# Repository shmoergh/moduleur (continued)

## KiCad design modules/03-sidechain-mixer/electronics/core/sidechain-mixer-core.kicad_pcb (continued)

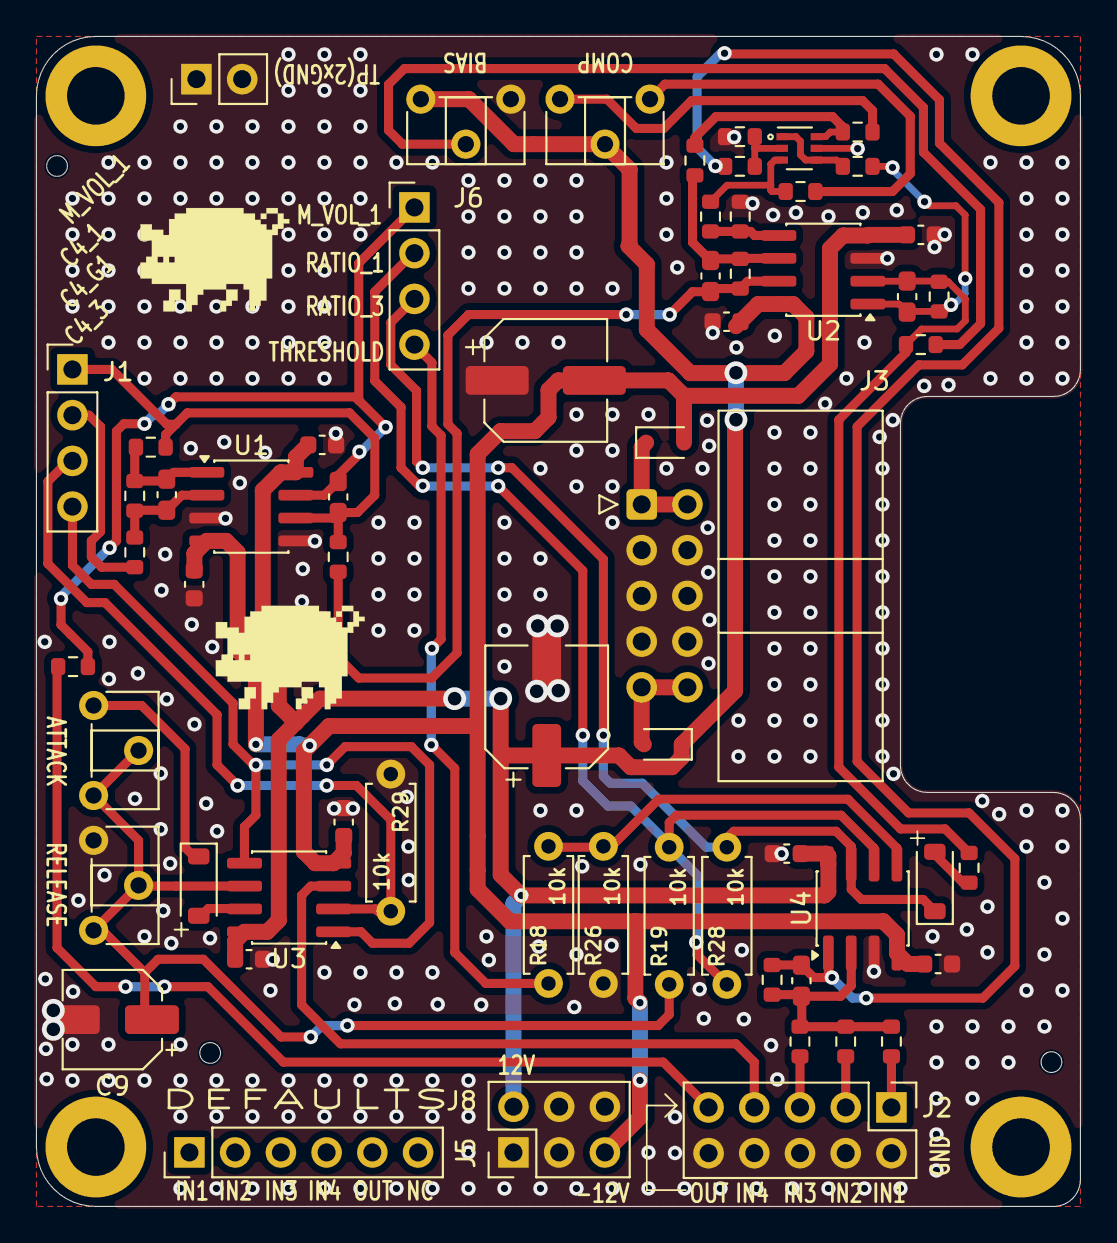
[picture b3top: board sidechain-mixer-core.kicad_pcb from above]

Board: 2 copper layers, 58.0 x 65.0 mm, 66 parts (0 on the bottom side), 39 nets.

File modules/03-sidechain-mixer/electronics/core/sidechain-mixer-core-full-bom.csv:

"Reference","Qty","Value","Exclude from BOM","Footprint","LCSC","Mouser Part no.","Part URL","Vendor","CHECKED"
"C1,C2,C3,C4,C5,C6,C7,C8","8","100n","","Capacitor_SMD:C_0603_1608Metric","C14663","","","JLCPCB","YES"
"C9","1","10u","","Capacitor_SMD:CP_Elec_5x5.4","C30110","","","JLCPCB","YES"
"C10,C11,C12,C13,C14","5","47p","","Capacitor_SMD:C_0603_1608Metric_Pad1.08x0.95mm_HandSolder","C1671","","","JLCPCB","YES"
"C23,C24","2","100u","","Capacitor_SMD:CP_Elec_6.3x7.7","C2836442","","","JLCPCB","YES"
"D1,D2","2","1N4148","","Diode_SMD:D_SOD-123","C81598","","","JLCPCB","YES"
"D6,D7","2","1N5817","","Diode_SMD:D_SOD-323","C5190152","","","JLCPCB","YES"
"J1,J6","2","Conn_01x04","","Connector_PinHeader_2.54mm:PinHeader_1x04_P2.54mm_Vertical","","200-HTSW10407TS ","https://mou.sr/3UfnMcJ","Mouser","YES"
"J2","1","Conn_02x05_Odd_Even","","Connector_PinHeader_2.54mm:PinHeader_2x05_P2.54mm_Vertical","","200-HTSW10507TD ","https://mou.sr/3MXhCO3","Mouser","YES"
"J3","1","Conn_02x05_Odd_Even","","Connector_IDC:IDC-Header_2x05_P2.54mm_Horizontal","","571-5103310-1","https://mou.sr/3GwYxj9","Mouser","YES"
"J4","1","Conn_01x02","","Connector_PinHeader_2.54mm:PinHeader_1x02_P2.54mm_Vertical","","200-HTSW10207TS","https://mou.sr/3IruU3e","Mouser","YES"
"J5","1","Conn_02x03_Odd_Even","","Connector_PinHeader_2.54mm:PinHeader_2x03_P2.54mm_Vertical","","200-TSW10307TD","https://mou.sr/4liCQlU","Mouser","YES"
"J8","1","Conn_01x06","","Connector_PinHeader_2.54mm:PinHeader_1x06_P2.54mm_Vertical","","200-HTSW10607TS","https://mou.sr/3YpdCIF","Mouser","YES"
"Q1","1","BC847BS","","Package_TO_SOT_SMD:SOT-363_SC-70-6","C5380687","","","JLCPCB","YES"
"R1,R2,R3,R4,R5,R6,R7,R9,R10,R16,R17","11","100k","","Resistor_SMD:R_0603_1608Metric","C25803","","","JLCPCB","YES"
"R8","1","220","","Resistor_SMD:R_0603_1608Metric","C22962","","","JLCPCB","YES"
"R11","1","1k","","Resistor_SMD:R_0603_1608Metric","C21190","","","JLCPCB","YES"
"R12,R21,R22","3","10k","","Resistor_SMD:R_0603_1608Metric","C25804","","","JLCPCB","YES"
"R13","1","33k","","Resistor_SMD:R_0603_1608Metric","C4216","","","JLCPCB","YES"
"R14,R15","2","200k","","Resistor_SMD:R_0603_1608Metric","C25811","","","JLCPCB","YES"
"R18,R19,R26,R28,R29","5","10k","","Shmoergh_Custom_Footprints:R_Axial_DIN0207_L6.3mm_D2.5mm_P7.62mm_Horizontal","","603-MFR-25FRF5210K","https://mou.sr/4aLzHIM","Mouser","YES"
"R23,R24","2","470k","","Resistor_SMD:R_0603_1608Metric","C23178","","","JLCPCB","YES"
"RV_ATTACK1,RV_RELEASE1","2","10-100k","","Potentiometer_THT:Potentiometer_ACP_CA6-H2,5_Horizontal","","774-06TR4AA103CP","https://mou.sr/44pTlq5","Mouser","YES"
"RV_BIAS1","1","100k","","Potentiometer_THT:Potentiometer_ACP_CA6-H2,5_Horizontal","","774-06TR4AA104CP","https://mou.sr/4oMQfnb","Mouser","YES"
"RV_COMP1","1","10k","","Potentiometer_THT:Potentiometer_ACP_CA6-H2,5_Horizontal","","774-06TR4AA103CP","https://mou.sr/44pTlq5","Mouser","YES"
"U1,U2,U3,U4","4","TL072","","Package_SO:SOIC-8_3.9x4.9mm_P1.27mm","C6961","","","JLCPCB","YES"
"H1,H2,H3,H4","4","MountingHole","Excluded from BOM","MountingHole:MountingHole_3.2mm_M3_DIN965_Pad","","","","Mouser",""

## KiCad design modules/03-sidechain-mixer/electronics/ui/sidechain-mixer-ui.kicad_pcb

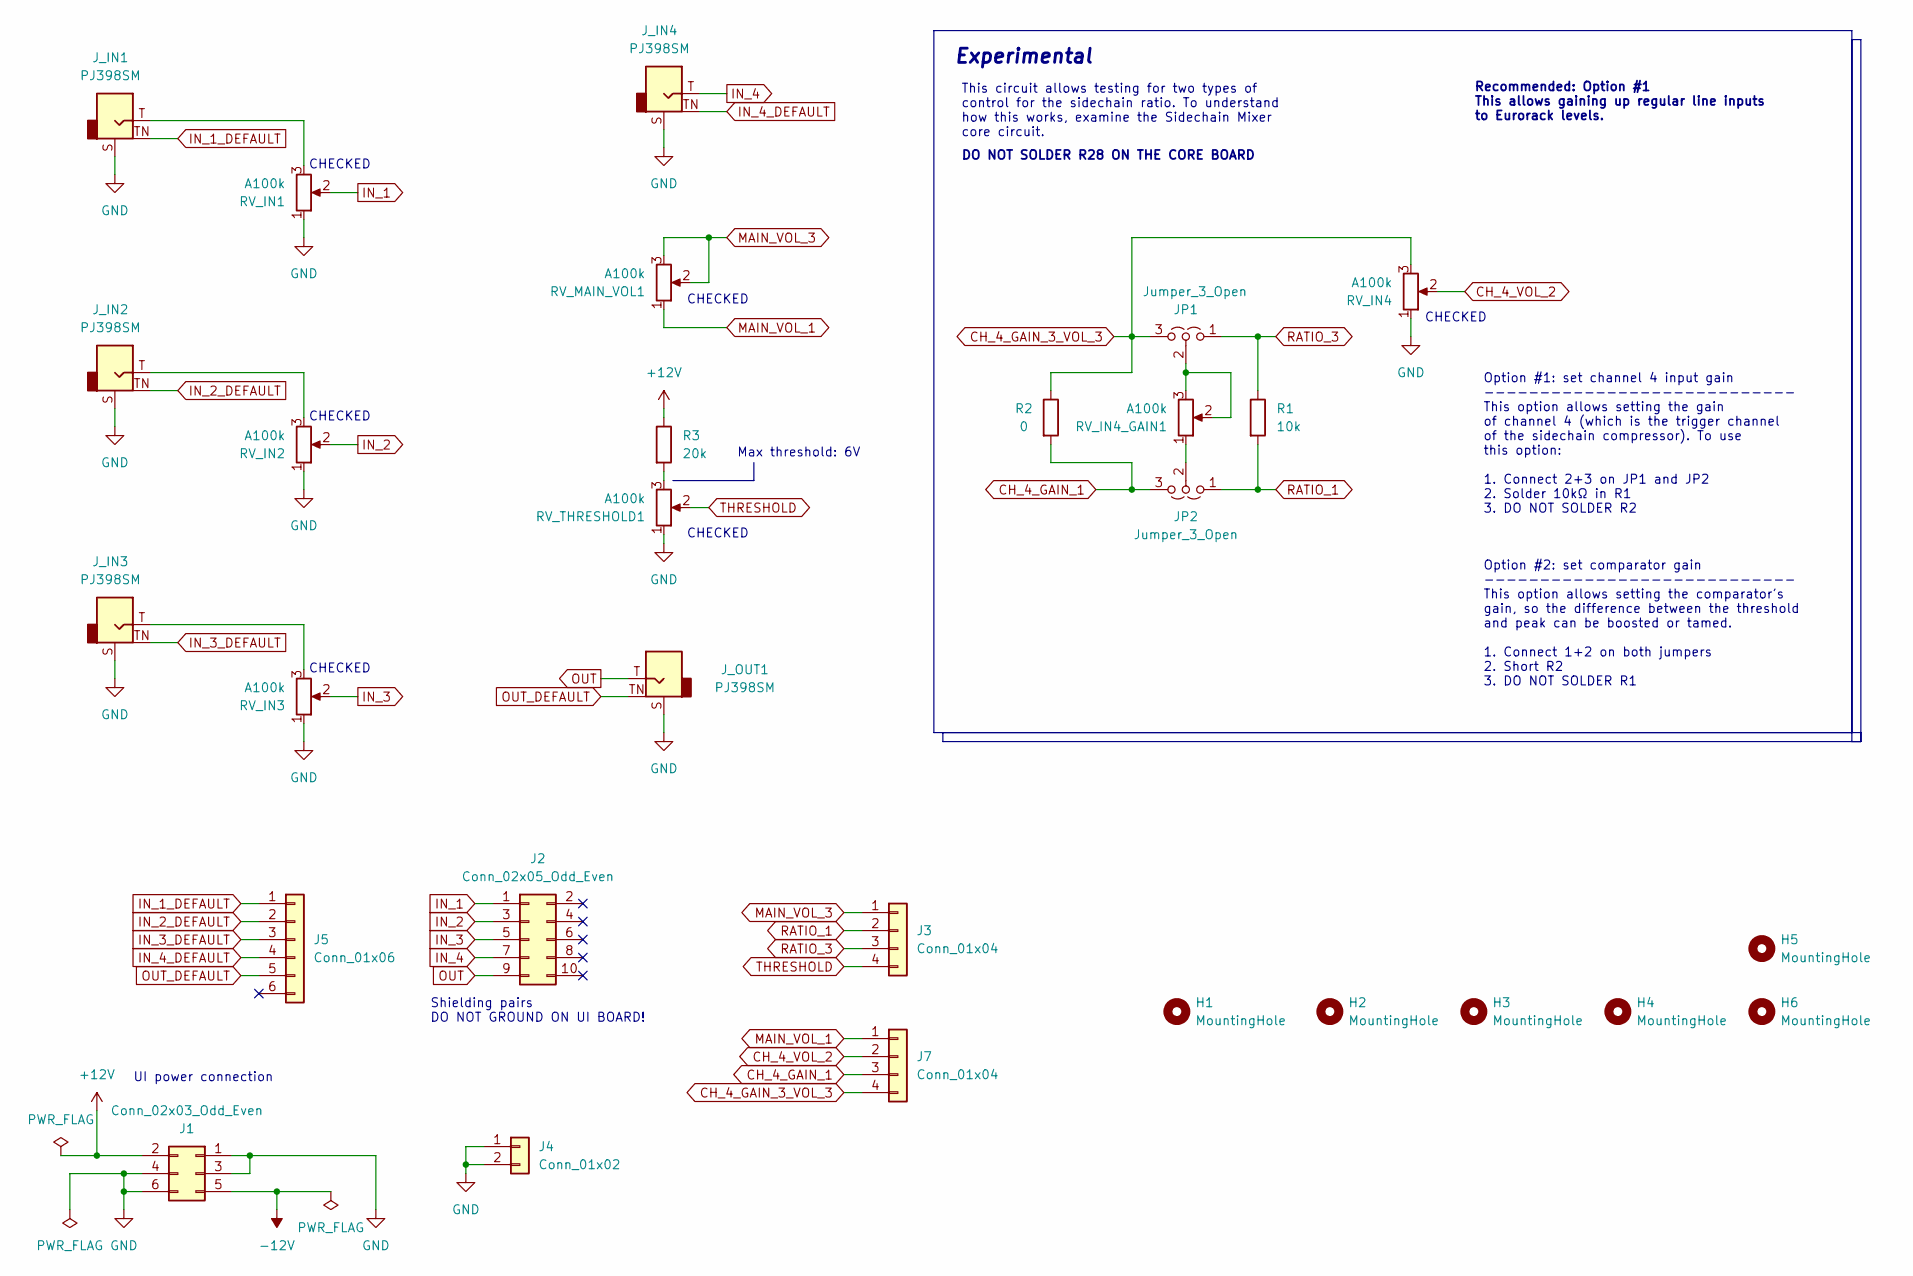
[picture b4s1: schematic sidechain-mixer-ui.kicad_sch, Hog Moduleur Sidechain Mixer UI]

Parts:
H1, H2, H3, H4, H5, H6: MountingHole; MountingHole_3.2mm_M3_DIN965_Pad
J1: Conn_02x03_Odd_Even; PinSocket_2x03_P2.54mm_Vertical; Part no. 200-SSW10301TD
J2: Conn_02x05_Odd_Even; PinSocket_2x05_P2.54mm_Vertical; Part no. 200-SSW10501TD
J3, J7: Conn_01x04; PinSocket_1x04_P2.54mm_Vertical; Part no. 200-SSW10401TMS
J4: Conn_01x02; PinSocket_1x02_P2.54mm_Vertical; Part no. 200-SSW10201TS
J5: Conn_01x06; PinSocket_1x06_P2.54mm_Vertical; Part no. 200-SSW10601TS
JP1, JP2: Jumper_3_Open; PinHeader_1x03_P2.54mm_Vertical
J_IN1, J_IN2, J_IN3, J_IN4: PJ398SM; Jack_3.5mm_QingPu_WQP-PJ398SM_Vertical_CircularHoles; Part no. PJ398SM
J_OUT1: PJ398SM; Jack_3.5mm_QingPu_WQP-PJ398SM_Vertical_CircularHoles; Part no. PJ398SM
R1: 10k; R_Axial_DIN0207_L6.3mm_D2.5mm_P7.62mm_Horizontal; Part no. 603-MFR-25FRF5210K
R2: 0; R_Axial_DIN0207_L6.3mm_D2.5mm_P7.62mm_Horizontal
R3: 20k; R_Axial_DIN0207_L6.3mm_D2.5mm_P7.62mm_Horizontal; Part no. 603-MFR-25FRF5220K
RV_IN1, RV_IN2, RV_IN3: A100k; TRIM_PTA3043-2010CIA503; Part no. 652-PTA30432015A104
RV_IN4, RV_IN4_GAIN1: A100k; Potentiometer_Bourns_Single-PTV09A; Part no. 652-PTV09A-4025UA104
RV_MAIN_VOL1: A100k; Potentiometer_Bourns_Single-PTV09A; Part no. 652-PTV09A-4025UA104
RV_THRESHOLD1: A100k; Potentiometer_Bourns_Single-PTV09A; Part no. 652-PTV09A-4025UA104

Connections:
+12V: J1.2, R3.1
-12V: J1.5
CH_4_GAIN_1: J7.3, JP2.3 (B), R2.2
CH_4_GAIN_3_VOL_3: J7.4, JP1.3 (B), R2.1, RV_IN4.3
CH_4_VOL_2: J7.2, RV_IN4.2
GND: J1.1, J1.3, J1.4, J1.6, J4.1, J4.2, J_IN1.S, J_IN2.S, J_IN3.S, J_IN4.S, J_OUT1.S, RV_IN1.1, RV_IN2.1, RV_IN3.1, RV_IN4.1, RV_THRESHOLD1.1
IN_1: J2.1, RV_IN1.2
IN_1_DEFAULT: J5.1, J_IN1.TN
IN_2: J2.3, RV_IN2.2
IN_2_DEFAULT: J5.2, J_IN2.TN
IN_3: J2.5, RV_IN3.2
IN_3_DEFAULT: J5.3, J_IN3.TN
IN_4: J2.7, J_IN4.T
IN_4_DEFAULT: J5.4, J_IN4.TN
MAIN_VOL_1: J7.1, RV_MAIN_VOL1.1
MAIN_VOL_3: J3.1, RV_MAIN_VOL1.2, RV_MAIN_VOL1.3
unnamed: JP1.2 (C), RV_IN4_GAIN1.2, RV_IN4_GAIN1.3
unnamed: JP2.2 (C), RV_IN4_GAIN1.1
unnamed: J_IN1.T, RV_IN1.3
unnamed: J_IN2.T, RV_IN2.3
unnamed: J_IN3.T, RV_IN3.3
unnamed: R3.2, RV_THRESHOLD1.3
OUT: J2.9, J_OUT1.T
OUT_DEFAULT: J5.5, J_OUT1.TN
RATIO_1: J3.2, JP2.1 (A), R1.2
RATIO_3: J3.3, JP1.1 (A), R1.1
THRESHOLD: J3.4, RV_THRESHOLD1.2

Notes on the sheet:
Recommended: Option #1 This allows gaining up regular line inputs to Eurorack levels.
Option #2: set comparator gain ---------------------------- This option allows setting the comparator's gain, so the difference between the threshold and peak can be boosted or tamed. 1. Connect 1+2 on both jumpers 2. Short R2 3. DO NOT SOLDER R1
Max threshold: 6V
CHECKED
This circuit allows testing for two types of control for the sidechain ratio. To understand how this works, examine the Sidechain Mixer core circuit.
UI power connection
Option #1: set channel 4 input gain ---------------------------- This option allows setting the gain of channel 4 (which is the trigger channel of the sidechain compressor). To use this option: 1. Connect 2+3 on JP1 and JP2 2. Solder 10kΩ in R1 3. DO NOT SOLDER R2
DO NOT SOLDER R28 ON THE CORE BOARD
Experimental
Shielding pairs DO NOT GROUND ON UI BOARD!

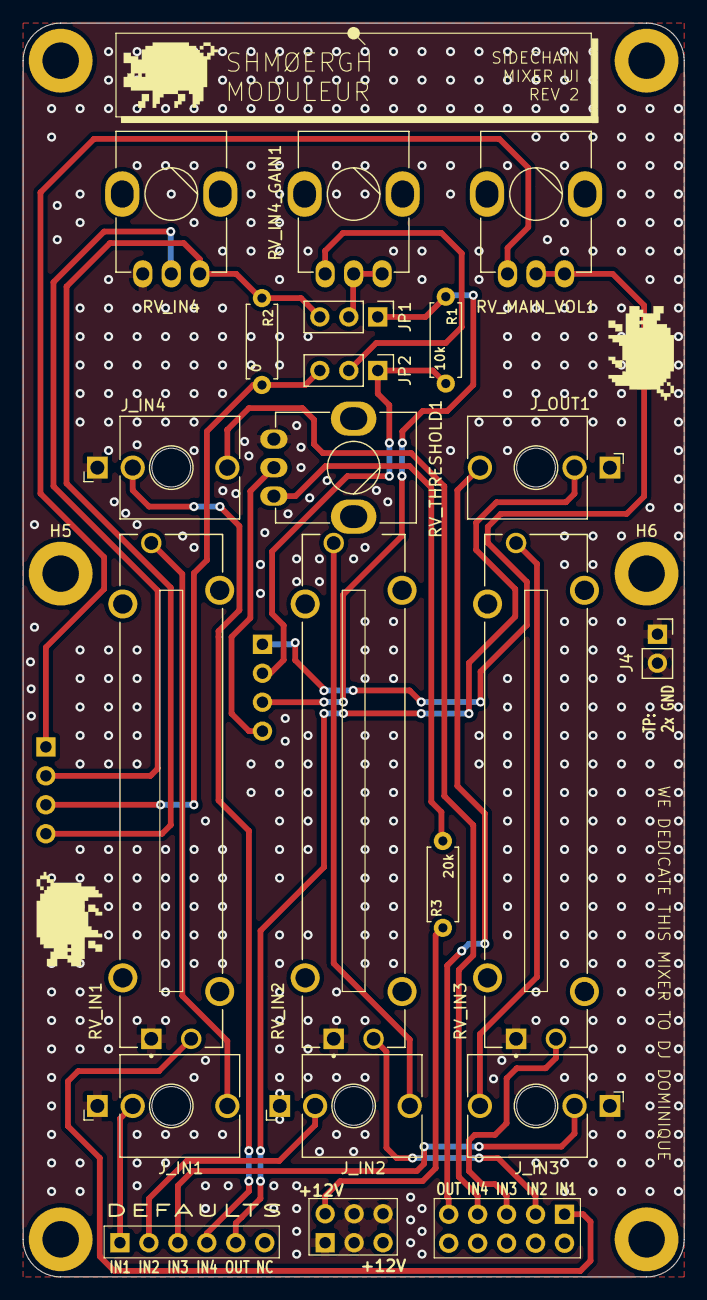
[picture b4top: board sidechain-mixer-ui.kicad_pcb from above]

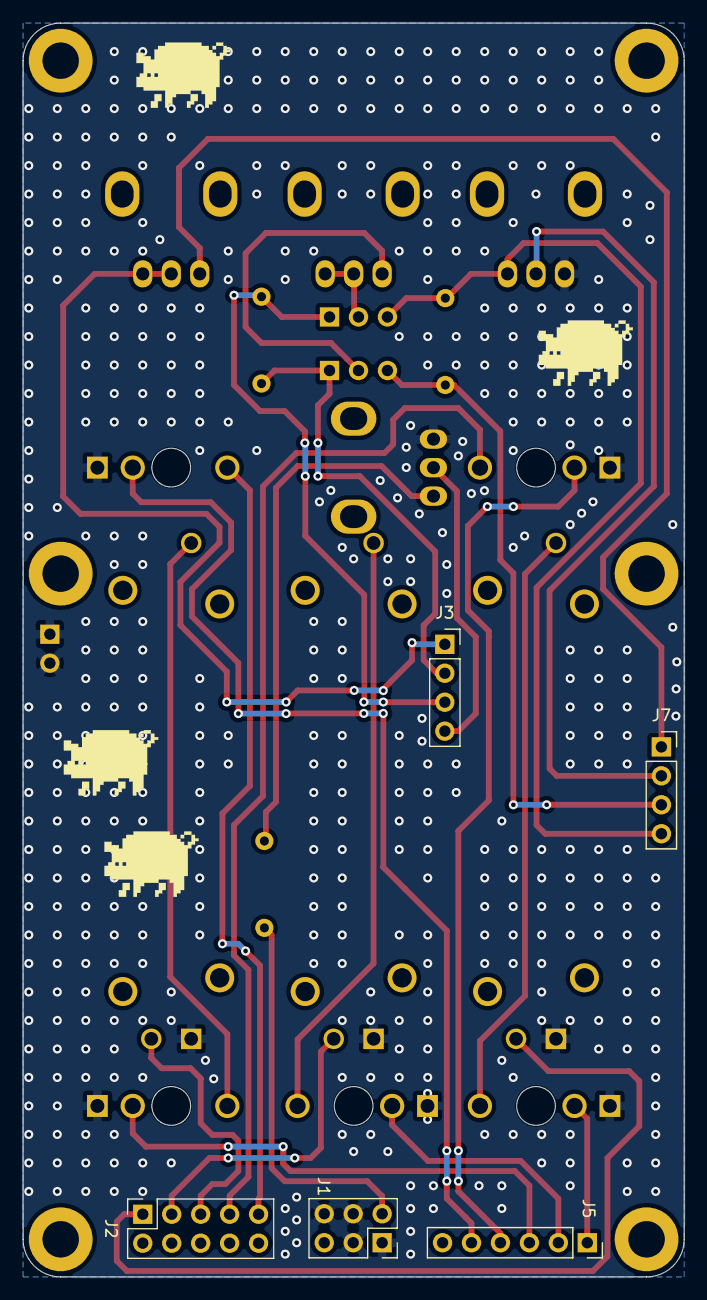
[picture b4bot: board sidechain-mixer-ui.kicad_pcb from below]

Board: 2 copper layers, 58.0 x 110.0 mm, 29 parts (5 on the bottom side), 26 nets.

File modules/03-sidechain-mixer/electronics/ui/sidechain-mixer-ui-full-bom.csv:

"Reference","Qty","Value","DNP","Exclude from BOM","Exclude from Board","Footprint","Datasheet","Part no.","Part URL","Vendor","Note"
"J1","1","Conn_02x03_Odd_Even","","","","Connector_PinSocket_2.54mm:PinSocket_2x03_P2.54mm_Vertical","~","200-SSW10301TD","https://mou.sr/3GIDVEr","Mouser",""
"J2","1","Conn_02x05_Odd_Even","","","","Connector_PinSocket_2.54mm:PinSocket_2x05_P2.54mm_Vertical","~","200-SSW10501TD","https://mou.sr/4lVCZM9","Mouser",""
"J3,J7","2","Conn_01x04","","","","Connector_PinSocket_2.54mm:PinSocket_1x04_P2.54mm_Vertical","~","200-SSW10401TMS","https://mou.sr/4kxE3Vr","Mouser",""
"J4","1","Conn_01x02","","","","Connector_PinSocket_2.54mm:PinSocket_1x02_P2.54mm_Vertical","~","200-SSW10201TS","https://mou.sr/4lBvdHe","Mouser",""
"J5","1","Conn_01x06","","","","Connector_PinSocket_2.54mm:PinSocket_1x06_P2.54mm_Vertical","~","200-SSW10601TS","https://mou.sr/4lnf48h","Mouser",""
"J_IN1,J_IN2,J_IN3,J_IN4,J_OUT1","5","PJ398SM","","","","Shmoergh_Custom_Footprints:Jack_3.5mm_QingPu_WQP-PJ398SM_Vertical_CircularHoles","~","PJ398SM","https://www.thonk.co.uk/shop/thonkiconn/","Thonk",""
"R1","1","10k","","","","Shmoergh_Custom_Footprints:R_Axial_DIN0207_L6.3mm_D2.5mm_P7.62mm_Horizontal","~","603-MFR-25FRF5210K","https://mou.sr/4aLzHIM","Mouser",""
"R2","1","0","","","","Shmoergh_Custom_Footprints:R_Axial_DIN0207_L6.3mm_D2.5mm_P7.62mm_Horizontal","~","","","",""
"R3","1","20k","","","","Shmoergh_Custom_Footprints:R_Axial_DIN0207_L6.3mm_D2.5mm_P7.62mm_Horizontal","~","603-MFR-25FRF5220K","https://mou.sr/3PSKVAZ","Mouser",""
"RV_IN1,RV_IN2,RV_IN3","3","A100k","","","","PTA3043-2010CIA503:TRIM_PTA3043-2010CIA503","~","652-PTA30432015A104 ","https://mou.sr/45jtvn7","Mouser",""
"RV_IN4,RV_IN4_GAIN1,RV_MAIN_VOL1,RV_THRESHOLD1","4","A100k","","","","Shmoergh_Custom_Footprints:Potentiometer_Bourns_Single-PTV09A","~","652-PTV09A-4025UA104 ","https://mou.sr/47O2sTG","Mouser","Knurled Shaft"

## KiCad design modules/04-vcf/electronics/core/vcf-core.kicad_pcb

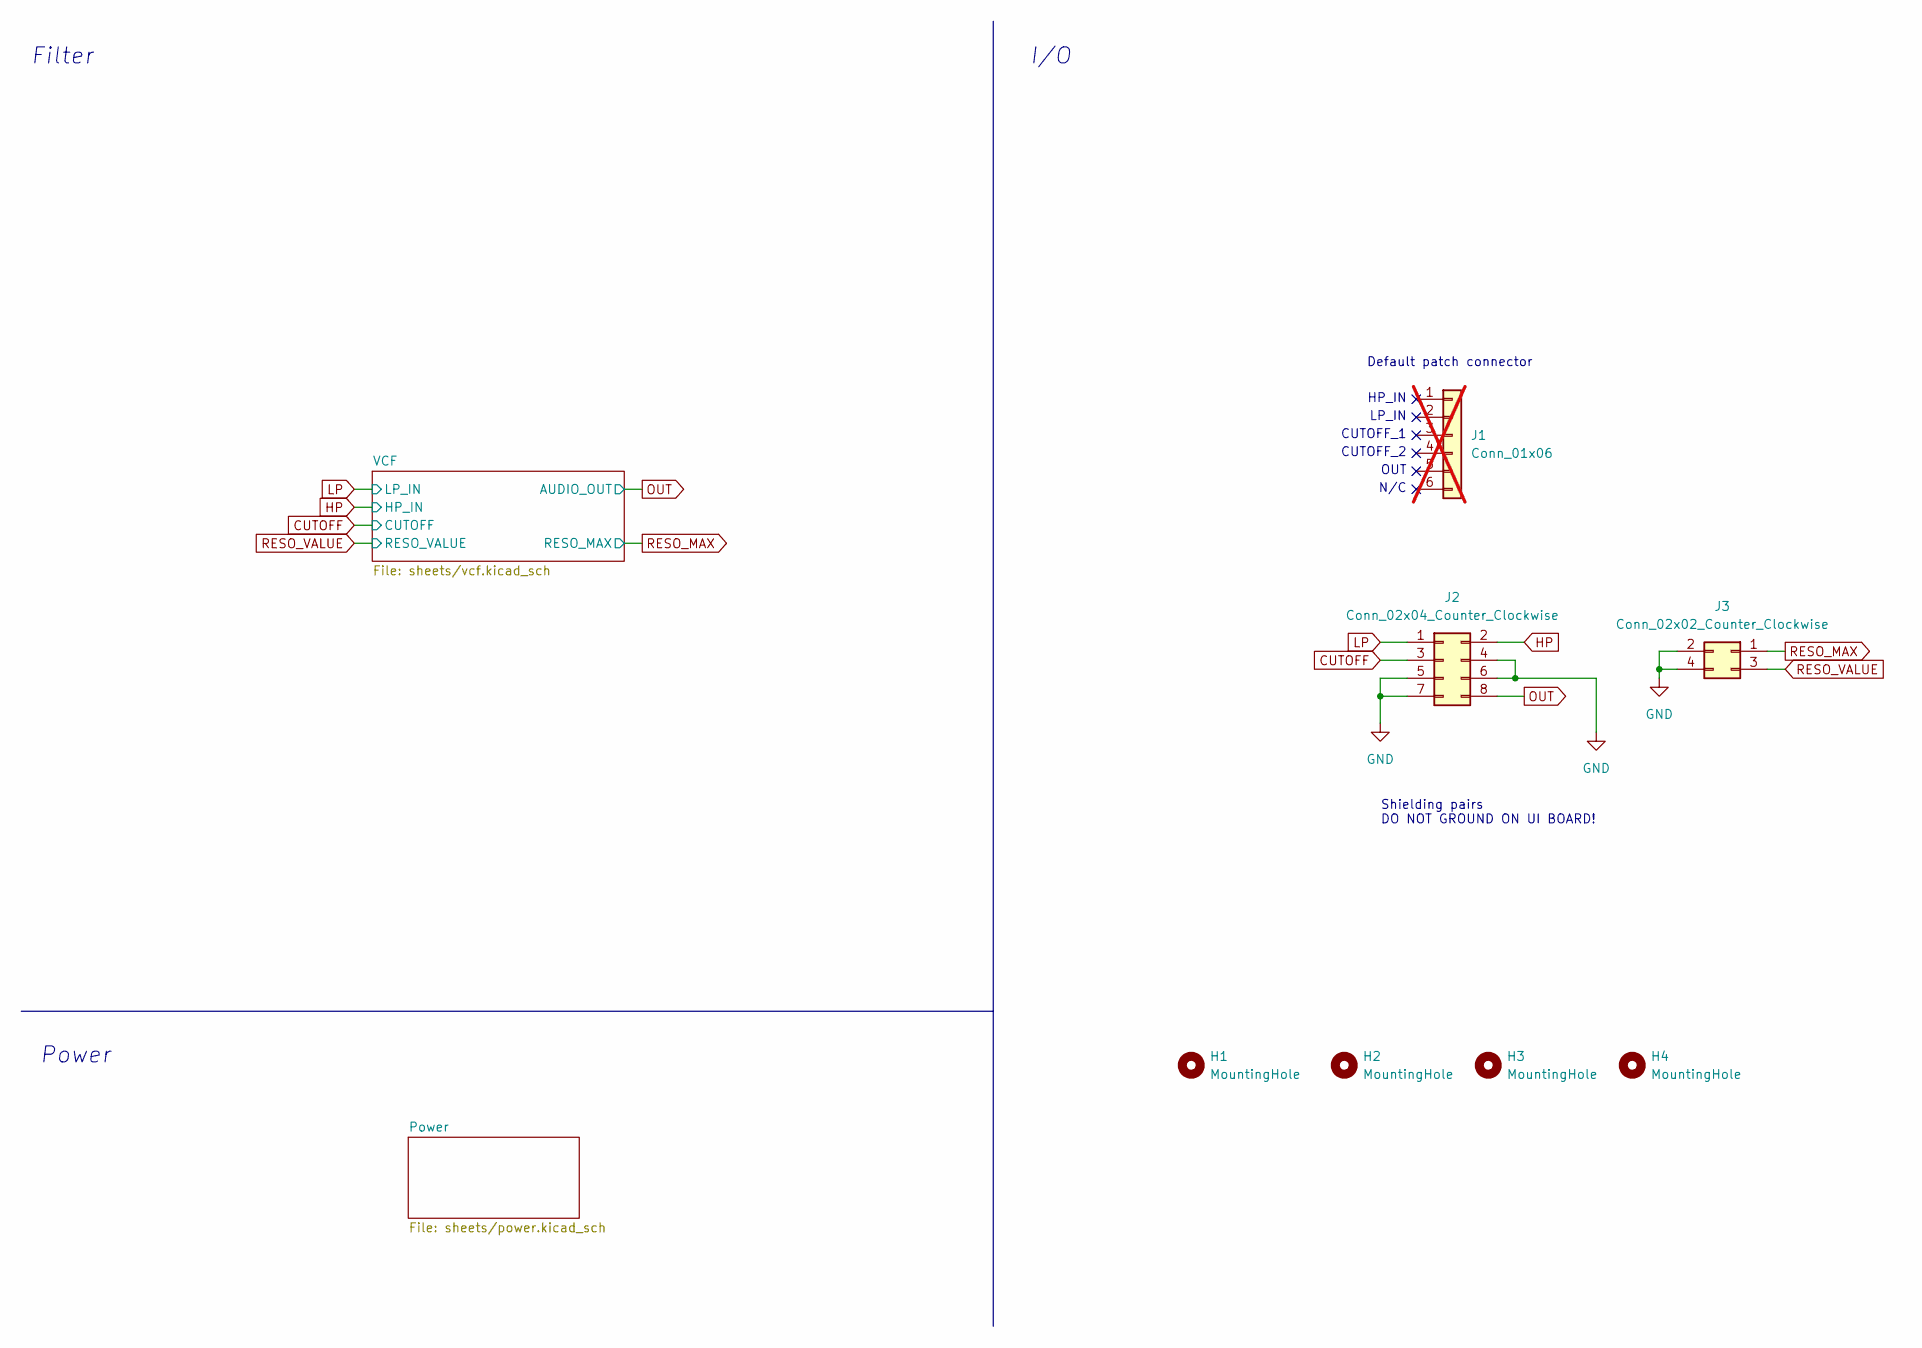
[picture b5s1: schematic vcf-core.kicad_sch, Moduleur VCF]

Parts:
H1, H2, H3, H4: MountingHole; MountingHole_3.2mm_M3_DIN965_Pad
J1: Conn_01x06; PinHeader_1x06_P2.54mm_Vertical; Part no. 200-SSW10401TMS; not fitted
J2: Conn_02x04_Counter_Clockwise; PinHeader_2x04_P2.54mm_Vertical; Part no. 200-HTSW10407TD
J3: Conn_02x02_Counter_Clockwise; PinHeader_2x02_P2.54mm_Vertical; Part no. 200-HTSW10207TD

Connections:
HP: J2.2; also elsewhere on the board
LP: J2.1; also elsewhere on the board
OUT: J2.8; also elsewhere on the board

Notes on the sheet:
Power
CUTOFF_1
Default patch connector
N/C
HP_IN
Shielding pairs DO NOT GROUND ON UI BOARD!
OUT
Filter
LP_IN
I/O
CUTOFF_2

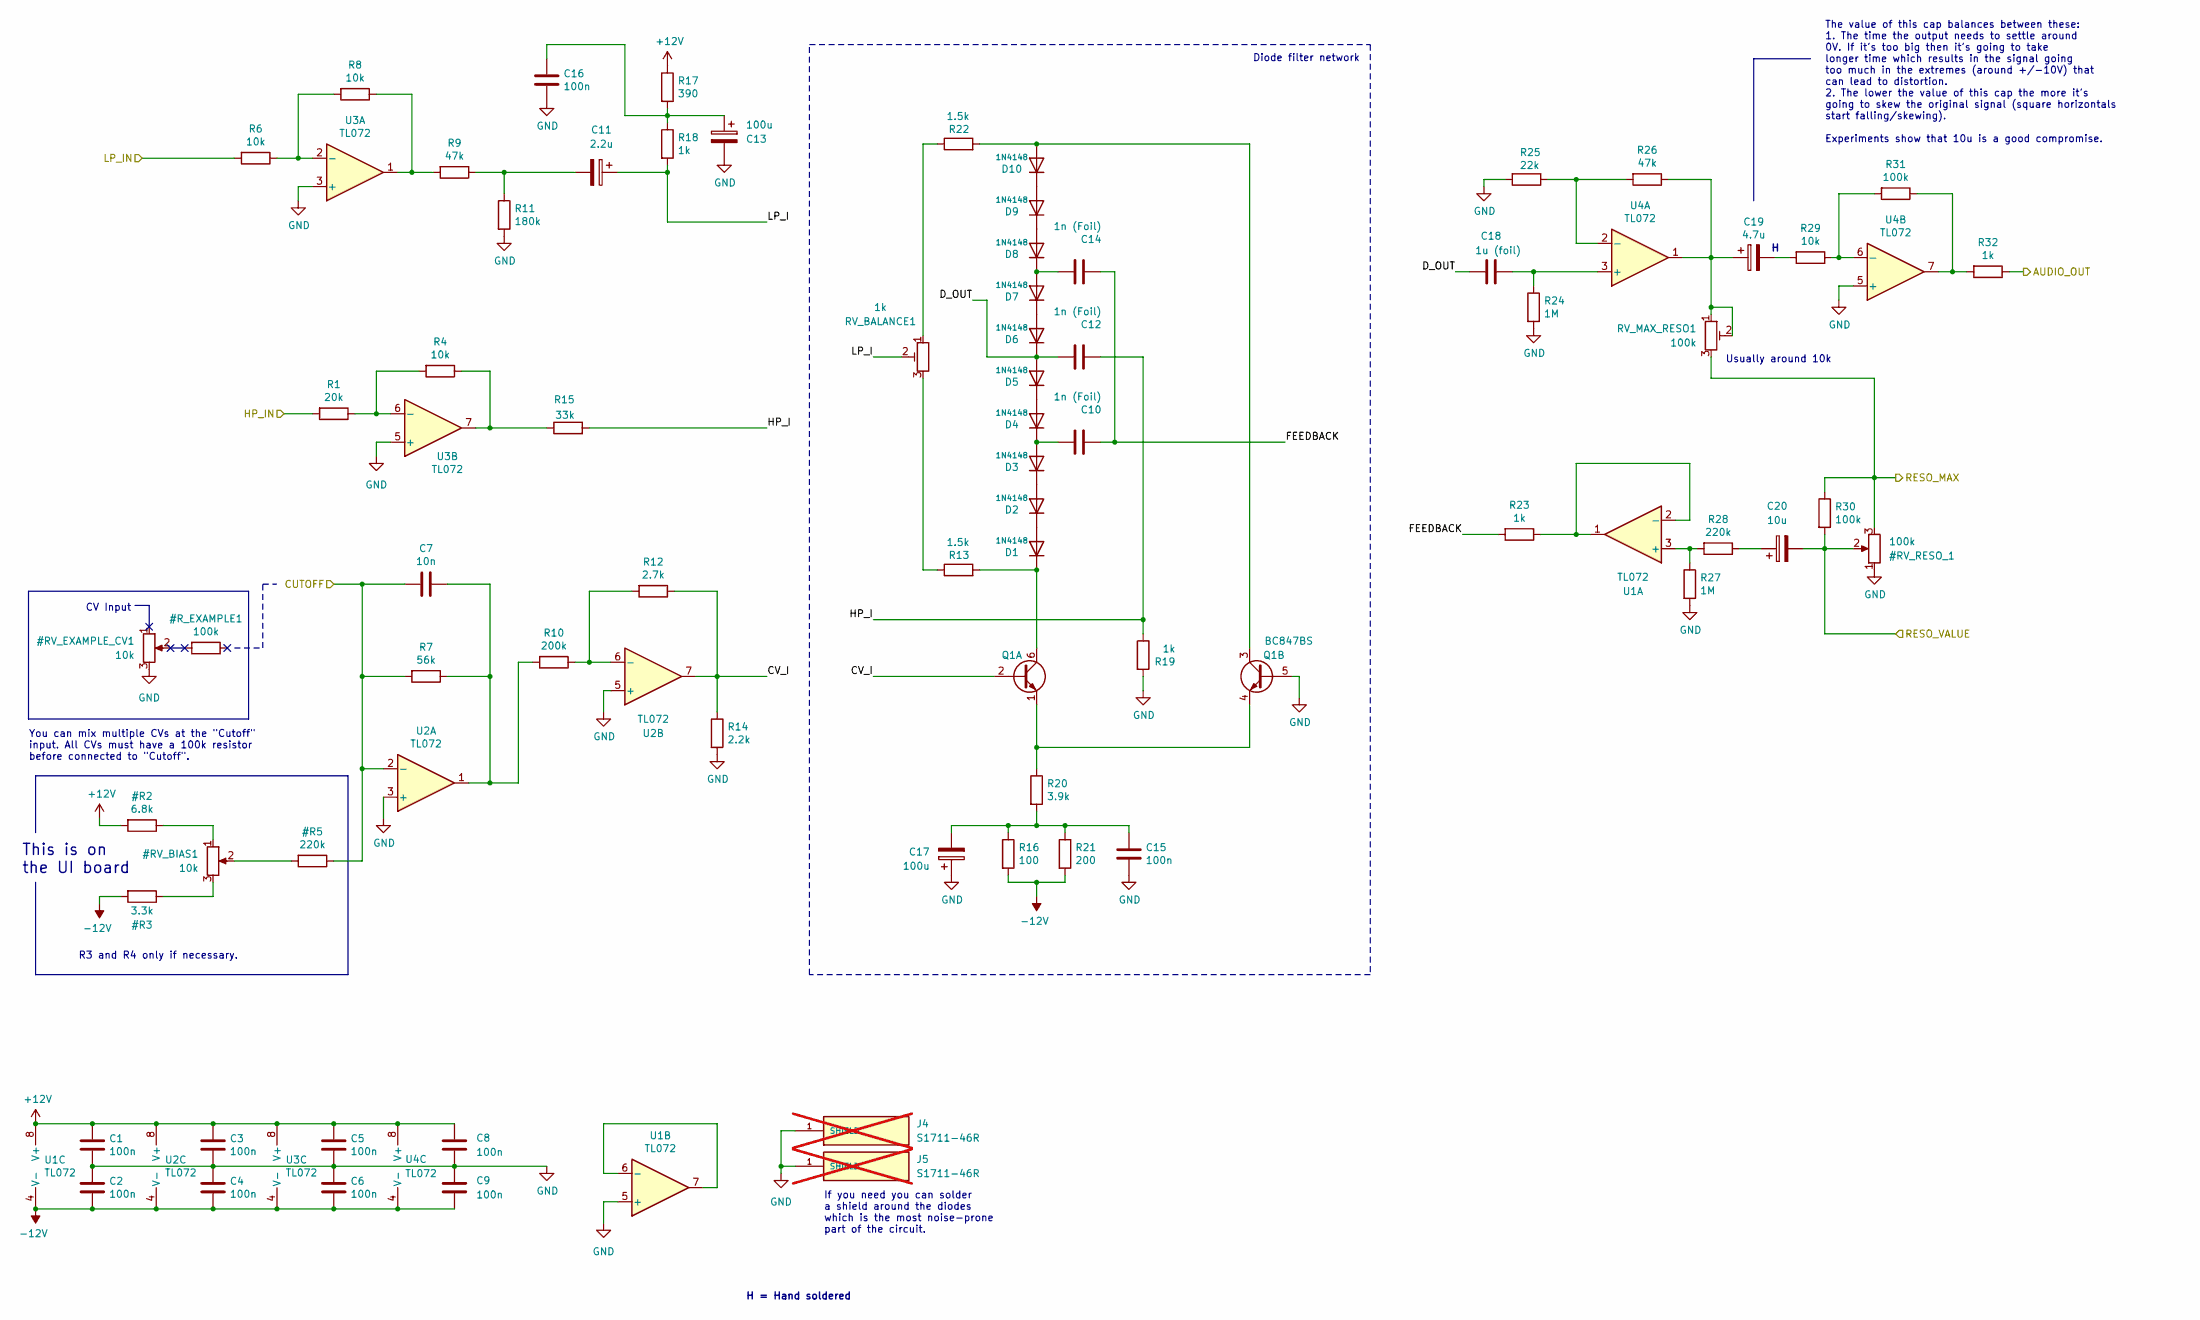
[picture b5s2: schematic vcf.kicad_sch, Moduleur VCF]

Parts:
C1, C2, C3, C4, C5, C6, C8, C9, C15, C16: 100n; C_0603_1608Metric; LCSC C14663
C7: 10n; C_0603_1608Metric; LCSC C57112
C10, C12, C14: 1n (Foil); C_Rect_L7.0mm_W2.5mm_P5.00mm; Part no. 80-R82EC1100SH50J
C11: 2.2u; CP_Elec_4x5.7; LCSC C249889
C13, C17: 100u; CP_Elec_6.3x7.7; LCSC C2836442
C18: 1u (foil); C_Rect_L7.0mm_W4.5mm_P5.00mm; Part no. 80-R82CC4100AA60J
C19: 4.7u; CP_Radial_D8.0mm_P5.00mm; Part no. 80-ESK475M035AC3AA
C20: 10u; CP_Elec_4x5.4; LCSC C3343
D1, D2, D3, D4, D5, D6, D7, D8, D9, D10: 1N4148; D_SOD-123; LCSC C81598
J4, J5: S1711-46R; HARWIN_S1711-46R; PARTREV 23/10/18; not fitted
Q1: BC847BS; SOT-363_SC-70-6; LCSC C5380687
R1: 20k; R_0603_1608Metric_Pad0.98x0.95mm_HandSolder; LCSC C4184
R4, R6, R8, R29: 10k; R_0603_1608Metric_Pad0.98x0.95mm_HandSolder; LCSC C25804
R7: 56k; R_0603_1608Metric_Pad0.98x0.95mm_HandSolder; LCSC C23206
R9, R26: 47k; R_0603_1608Metric_Pad0.98x0.95mm_HandSolder; LCSC C25819
R10: 200k; R_0603_1608Metric_Pad0.98x0.95mm_HandSolder; LCSC C25811
R11: 180k; R_0603_1608Metric_Pad0.98x0.95mm_HandSolder; LCSC C3016400
R12: 2.7k; R_0603_1608Metric_Pad0.98x0.95mm_HandSolder; LCSC C13167
R13, R22: 1.5k; R_0603_1608Metric_Pad0.98x0.95mm_HandSolder; LCSC C22843
R14: 2.2k; R_0603_1608Metric_Pad0.98x0.95mm_HandSolder; LCSC C4190
R15: 33k; R_0603_1608Metric_Pad0.98x0.95mm_HandSolder; LCSC C4216
R16: 100; R_0603_1608Metric_Pad0.98x0.95mm_HandSolder; LCSC C22775
R17: 390; R_0603_1608Metric_Pad0.98x0.95mm_HandSolder; LCSC C23151
R18, R19, R23, R32: 1k; R_0603_1608Metric_Pad0.98x0.95mm_HandSolder; LCSC C21190
R20: 3.9k; R_0603_1608Metric_Pad0.98x0.95mm_HandSolder; LCSC C23018
R21: 200; R_0603_1608Metric_Pad0.98x0.95mm_HandSolder; LCSC C8218
R24, R27: 1M; R_0603_1608Metric_Pad0.98x0.95mm_HandSolder; LCSC C22935
R25: 22k; R_0603_1608Metric_Pad0.98x0.95mm_HandSolder; LCSC C31850
R28: 220k; R_0603_1608Metric_Pad0.98x0.95mm_HandSolder; LCSC C22961
R30, R31: 100k; R_0603_1608Metric_Pad0.98x0.95mm_HandSolder; LCSC C25803
RV_BALANCE1: 1k; Potentiometer_ACP_CA6-H2,5_Horizontal; Part no. 531-PT6KH-1K
RV_MAX_RESO1: 100k; Potentiometer_ACP_CA6-H2,5_Horizontal; Part no. 774-06TR4AA104CP
U1, U2, U3, U4: TL072; SOIC-8_3.9x4.9mm_P1.27mm; LCSC C6961

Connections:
/VCF/CV_I: Q1.2 (B1), R12.1, R14.1, U2.7
/VCF/D_OUT: C12.1, C18.2, D5.2 (A), D6.1 (K)
/VCF/FEEDBACK: C10.2, C14.2, R23.2
/VCF/HP_I: C12.2, R15.2, R19.1
/VCF/LP_I: C11.1, R18.2, RV_BALANCE1.2
HP: R1.2; also elsewhere on the board
LP: R6.2; also elsewhere on the board
unnamed: C7.1, R7.1, R10.2, U2.1
unnamed: C11.2, R9.1, R11.1
unnamed: C13.1, C16.1, R17.2, R18.1
unnamed: C15.1, C17.2, R16.1, R20.2, R21.1
unnamed: C19.1, R26.1, RV_MAX_RESO1.1, RV_MAX_RESO1.2, U4.1
unnamed: C19.2, R29.2
unnamed: C20.1, R28.1
unnamed: D1.2 (A), D2.1 (K)
unnamed: D1.1 (K), Q1.6 (C1), R13.2
unnamed: D2.2 (A), D3.1 (K)
unnamed: C10.1, D3.2 (A), D4.1 (K)
unnamed: D4.2 (A), D5.1 (K)
unnamed: D6.2 (A), D7.1 (K)
unnamed: C14.1, D7.2 (A), D8.1 (K)
unnamed: D8.2 (A), D9.1 (K)
unnamed: D10.2 (A), Q1.3 (C2), R22.2
unnamed: D9.2 (A), D10.1 (K)
unnamed: Q1.1 (E1), Q1.4 (E2), R20.1
unnamed: R8.1, R9.2, U3.1
unnamed: R13.1, RV_BALANCE1.3
unnamed: R4.1, R15.1, U3.7
unnamed: R22.1, RV_BALANCE1.1
unnamed: R31.1, R32.2, U4.7
unnamed: R27.1, R28.2, U1.3 (+)
unnamed: R23.1, U1.1, U1.2 (-)
unnamed: U1.6 (-), U1.7
unnamed: R10.1, R12.2, U2.6 (-)
unnamed: R6.1, R8.2, U3.2 (-)
unnamed: R1.1, R4.2, U3.6 (-)
unnamed: C18.1, R24.1, U4.3 (+)
unnamed: R25.1, R26.2, U4.2 (-)
unnamed: R29.1, R31.2, U4.6 (-)
OUT: R32.1; also elsewhere on the board

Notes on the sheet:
R3 and R4 only if necessary.
CV Input
If you need you can solder a shield around the diodes which is the most noise-prone part of the circuit.
This is on the UI board
Diode filter network
You can mix multiple CVs at the "Cutoff" input. All CVs must have a 100k resistor before connected to "Cutoff".
The value of this cap balances between these: 1. The time the output needs to settle around 0V. If it's too big then it's going to take longer time which results in the signal going too much in the extremes (around +/-10V) that can lead to distortion. 2. The lower the value of this cap the more it'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
Usually around 10k
H = Hand soldered

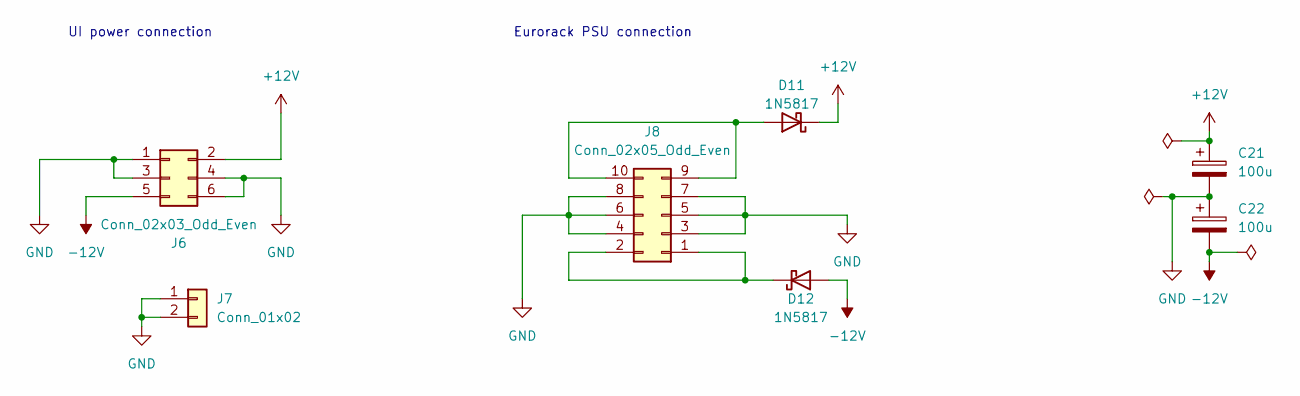
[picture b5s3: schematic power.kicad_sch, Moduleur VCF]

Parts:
C21, C22: 100u; CP_Elec_6.3x7.7; LCSC C2836442
D11, D12: 1N5817; D_SOD-323; LCSC C5190152
J6: Conn_02x03_Odd_Even; PinHeader_2x03_P2.54mm_Vertical; Part no. 200-TSW10307TD
J7: Conn_01x02; PinHeader_1x02_P2.54mm_Vertical; Part no. 200-HTSW10207TS
J8: Conn_02x05_Odd_Even; IDC-Header_2x05_P2.54mm_Horizontal; Part no. 571-5103310-1

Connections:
unnamed: D11.2 (A), J8.9, J8.10
unnamed: D12.1 (K), J8.1, J8.2

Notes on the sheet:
UI power connection
Eurorack PSU connection

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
